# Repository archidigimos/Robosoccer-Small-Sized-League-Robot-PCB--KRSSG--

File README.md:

# Robosoccer-Small-Sized-League-Robot-PCB--KRSSG--
PCB for autonomous soccer playing robots. The PCBs are assembled in deck form.

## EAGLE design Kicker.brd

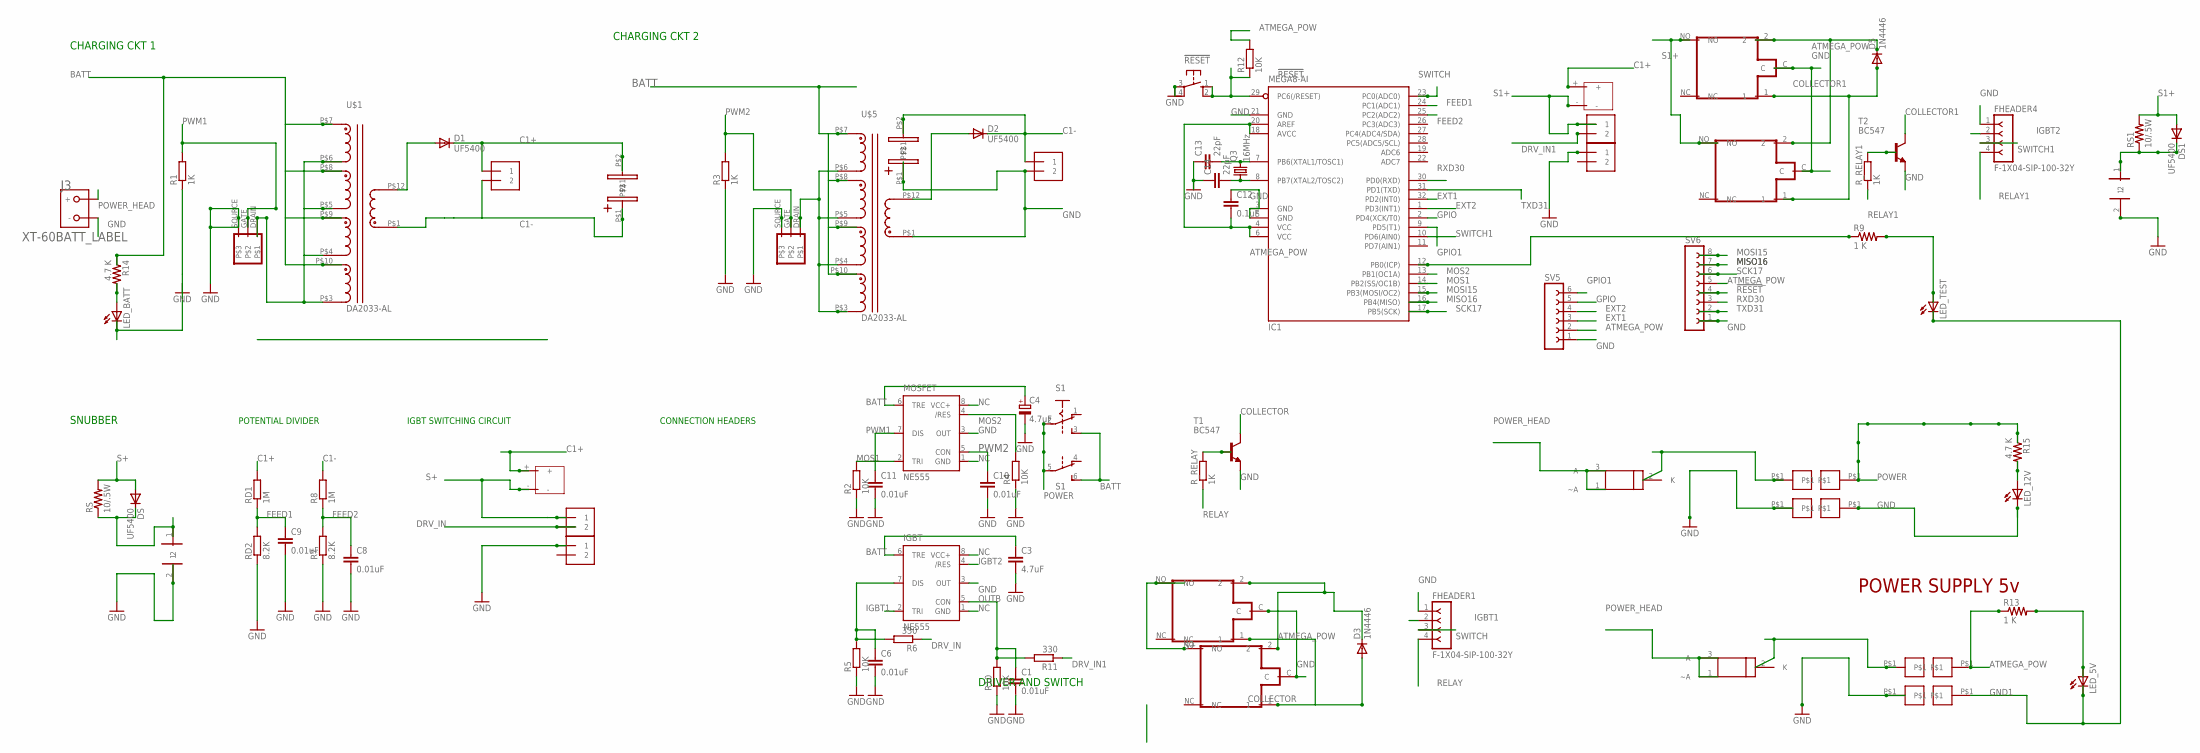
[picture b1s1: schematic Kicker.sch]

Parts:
5V: PINHEAD_1
!RESET: 10-XX; B3F-10XX
C1, C6, C8, C9, C10, C11: 0.01uF; C1206
C3: 4.7uF; C1206
C4: 4.7uF; E2,5-6
C12: 0.1uF; C1206
C13, C14: 22pF; C1206
D1, D2: UF5400; DO201-15
D3, D5: 1N4446; DO35-10
DS, DS1: UF5400; DO201-15
FHEADER1, FHEADER4: F-1X04-SIP-100-32Y; SIP-100-04-32Y
GND, GND12: PINHEAD_1
GND_5V, GND_12V1: PINHEAD_1
IC1: MEGA8-AI; TQFP32-08
IGBT: NE555; DIL-08
J1, J2, J4, J5, J6, J7: 1X2-3.5MM
J3: XT-60BATT_LABEL; XT-60
LED_5V, LED_12V: LEDSML1206; SML1206
LED_BATT: LEDSML1206; SML1206
LED_TEST: LEDSML1206; SML1206
MOSFET: NE555; DIL-08
POWER_1: PINHEAD_1
POWER_HEAD1: PINHEAD_1
Q3: 16MHz; HC49U70
R1, R3: 1K; R1206
R2, R4, R5, R10, R12: 10K; R1206
R6, R11: 330; R1206
R7: 8.2K; R1206
R8: 1M; R1206
R9, R13: 1 K; 0805-THM
R14, R15: 4.7 K; 0805-THM
RD1: 1M; R1206
RD2: 8.2K; R1206
RS, RS1: 10/.5W; 0411/15
R_RELAY, R_RELAY1: 1K; R1206
S1: A68-A31
SV5: FE06-1; FE06
SV6: FE08-1; FE08
T1, T2: BC547; TO92
U1, U4: LP38690DT-3.3; TO228P1042X238-3N
U$1, U$5: DA2033-AL
U$2, U$4: CAPS; CAP
U$3, U$9: MOS
U$6, U$16: SCREW
U$7, U$8: POLYCAP
U$10, U$11, U$12, U$13: REL
V_BAT: PINHEAD_1

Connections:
!RESET: !RESET.1 (S), !RESET.2 (S1), IC1.29 (PC6(/RESET)), R12.1, SV6.4
ATMEGA_POW: 5V.P$1, C12.2, D3.C, D5.C, IC1.4 (VCC), IC1.6 (VCC), IC1.18 (AVCC), IC1.20 (AREF), R12.2, R13.1, SV5.2, SV6.5, U$10.2, U$11.2, U$12.2, U$13.2
BATT: C3.1, C4.+, IGBT.6 (TRE), MOSFET.6 (TRE), R14.1, S1.3 (S), S1.6 (S), U$1.P$7 (7), U$1.P$8 (8), U$1.P$9 (9), U$1.P$10 (10), U$5.P$7 (7), U$5.P$8 (8), U$5.P$9 (9), U$5.P$10 (10)
C1+: D1.C, J2.1, RD1.2, U$2.P$2, U$6.+, U$16.+
C1-: D2.C, J1.1, J2.2, R8.2, U$1.P$1 (1), U$2.P$1, U$4.P$2
COLLECTOR: D3.A, T1.3 (C), U$10.1, U$12.1
COLLECTOR1: D5.A, T2.3 (C), U$11.1, U$13.1
DRV_IN: J6.2, R6.1
DRV_IN1: J4.2, R11.1
EXT1: IC1.32 (PD2(INT0)), SV5.3
EXT2: IC1.1 (PD3(INT1)), SV5.4
FEED1: C9.1, IC1.24 (PC1(ADC1)), RD1.1, RD2.2
FEED2: C8.1, IC1.25 (PC2(ADC2)), R7.2, R8.1
GND: !RESET.3, !RESET.4 (P1), C1.2, C3.2, C4.-, C6.2, C8.2, C9.2, C10.2, C11.2, C12.1, C13.1, C14.1, FHEADER1.1, FHEADER4.1, GND12.P$1, GND_5V.P$1, GND_12V1.P$1, IC1.3 (GND), IC1.5 (GND), IC1.21 (GND), IGBT.3 (OUT), J1.2, J3.GND (-), J5.1, J7.1, LED_12V.C, LED_BATT.C, MOSFET.3 (OUT), R1.1, R2.1, R3.1, R4.1, R5.1, R7.1, R10.1, RD2.1, SV5.1, SV6.1, T1.1 (E), T2.1 (E), U$3.SOURCE, U$4.P$1, U$5.P$1 (1), U$7.2, U$8.2, U$9.SOURCE, U$10.C, U$11.C, U$12.C, U$13.C
GND1: GND.P$1, LED_5V.C, LED_TEST.C
GPIO: IC1.2 (PD4(XCK/T0)), SV5.5
GPIO1: IC1.9 (PD5(T1)), SV5.6
IGBT1: FHEADER1.2, IGBT.2 (TRI)
IGBT2: FHEADER4.2, IGBT.4 (/RES)
MISO16: IC1.16 (PB4(MISO)), SV6.7
MOS1: IC1.14 (PB2(SS/OC1B)), MOSFET.2 (TRI), R2.2
MOS2: IC1.13 (PB1(OC1A)), MOSFET.4 (/RES), R4.2
MOSI15: IC1.15 (PB3(MOSI/OC2)), SV6.8
unnamed: DS.C, RS.1, U$7.1
unnamed: R_RELAY.2, T1.2 (B)
unnamed: C6.1, IGBT.7 (DIS), R5.2, R6.2
unnamed: D2.A, U$5.P$12 (12)
unnamed: LED_5V.A, R13.2
unnamed: POWER_HEAD1.P$1, U1.2 (K)
unnamed: D1.A, U$1.P$12 (12)
unnamed: DS1.C, RS1.1, U$8.1
unnamed: R_RELAY1.2, T2.2 (B)
unnamed: LED_BATT.A, R14.2
unnamed: C13.2, IC1.7 (PB6(XTAL1/TOSC1)), Q3.2
unnamed: LED_12V.A, R15.2
unnamed: U4.2 (K), V_BAT.P$1
unnamed: C14.2, IC1.8 (PB7(XTAL2/TOSC2)), Q3.1
unnamed: LED_TEST.A, R9.2
unnamed: U$5.P$3 (3), U$5.P$4 (4), U$5.P$5 (5), U$5.P$6 (6), U$9.DRAIN
unnamed: U$1.P$3 (3), U$1.P$4 (4), U$1.P$5 (5), U$1.P$6 (6), U$3.DRAIN
unnamed: IC1.12 (PB0(ICP)), R9.1
NC: IGBT.1 (GND), IGBT.8 (VCC+), MOSFET.1 (GND), MOSFET.8 (VCC+)
OUTB: C1.1, IGBT.5 (CON), R10.2, R11.2
POWER: POWER_1.P$1, R15.1, S1.2, S1.5
POWER_HEAD: J3.BATT (+), U1.1 (~A), U1.3 (A), U4.1 (~A), U4.3 (A)
PWM1: C11.1, MOSFET.7 (DIS), R1.2, U$3.GATE
PWM2: C10.1, MOSFET.5 (CON), R3.2, U$9.GATE
RELAY: FHEADER1.4, R_RELAY.1
RELAY1: FHEADER4.4, R_RELAY1.1
RXD30: IC1.30 (PD0(RXD)), SV6.3
S1+: DS1.A, J4.1, RS1.2, U$6.-, U$11.NO, U$13.NO
S+: DS.A, J6.1, RS.2, U$10.NO, U$12.NO, U$16.-
SCK17: IC1.17 (PB5(SCK)), SV6.6
SWITCH: FHEADER1.3, IC1.23 (PC0(ADC0))
SWITCH1: FHEADER4.3, IC1.10 (PD6(AIN0))
TXD31: IC1.31 (PD1(TXD)), SV6.2

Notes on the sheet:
SNUBBER
CHARGING CKT 1
CHARGING CKT 2
POTENTIAL DIVIDER
IGBT SWITCHING CIRCUIT
CONNECTION HEADERS
DRIVER AND SWITCH
POWER SUPPLY 5v

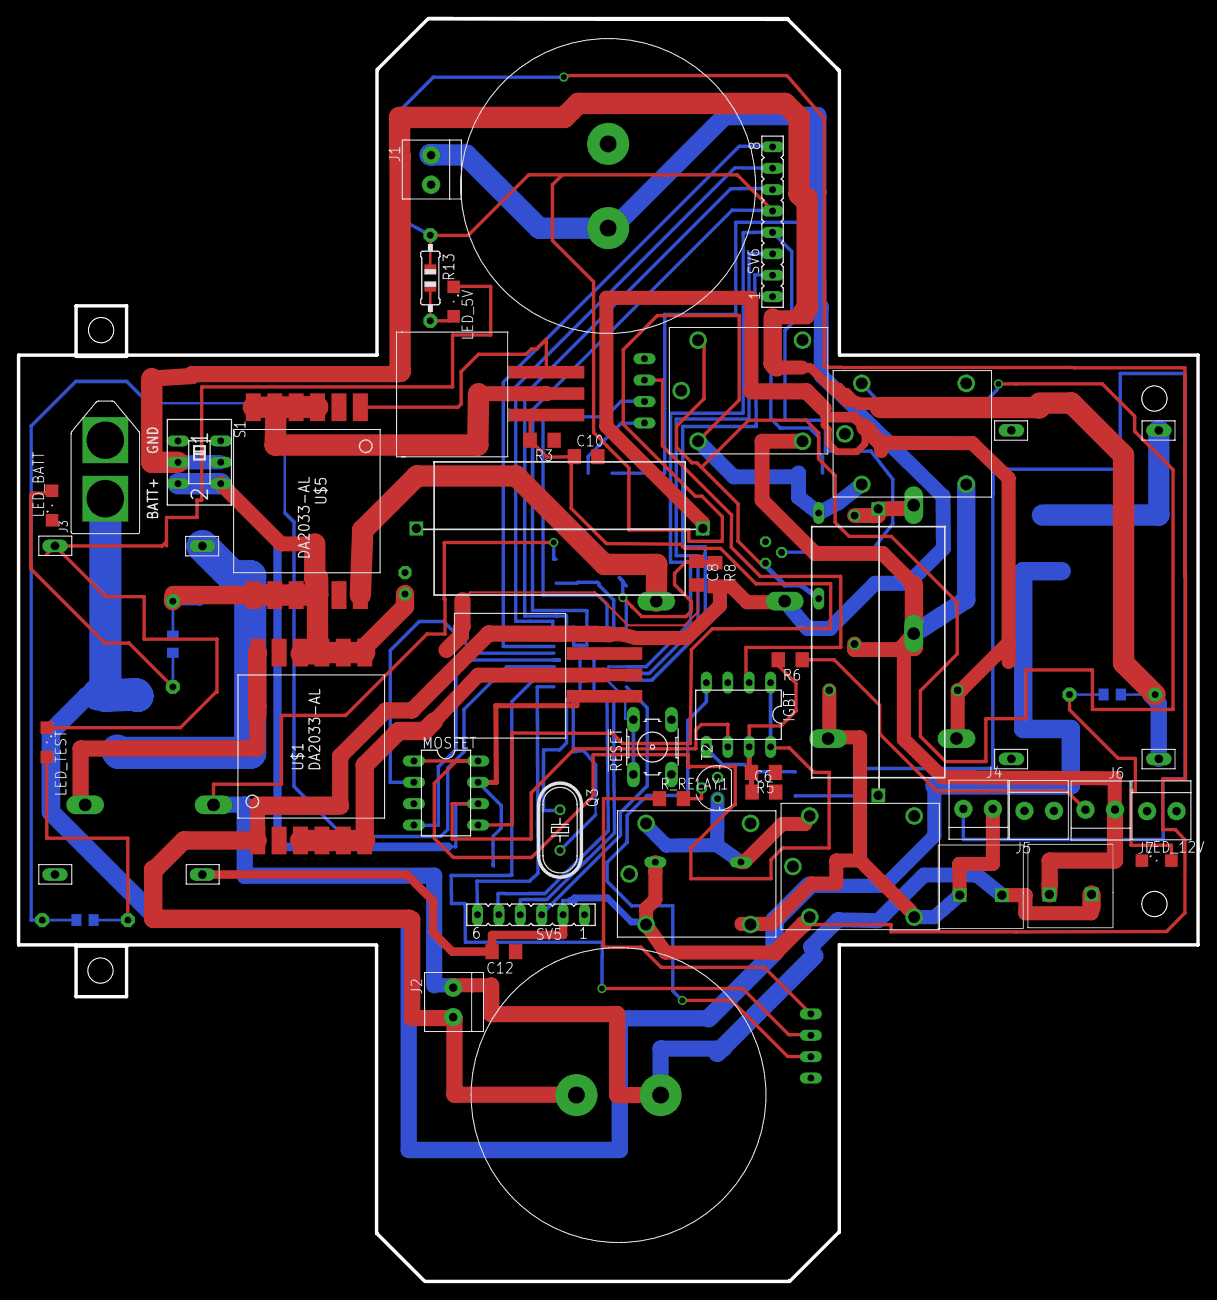
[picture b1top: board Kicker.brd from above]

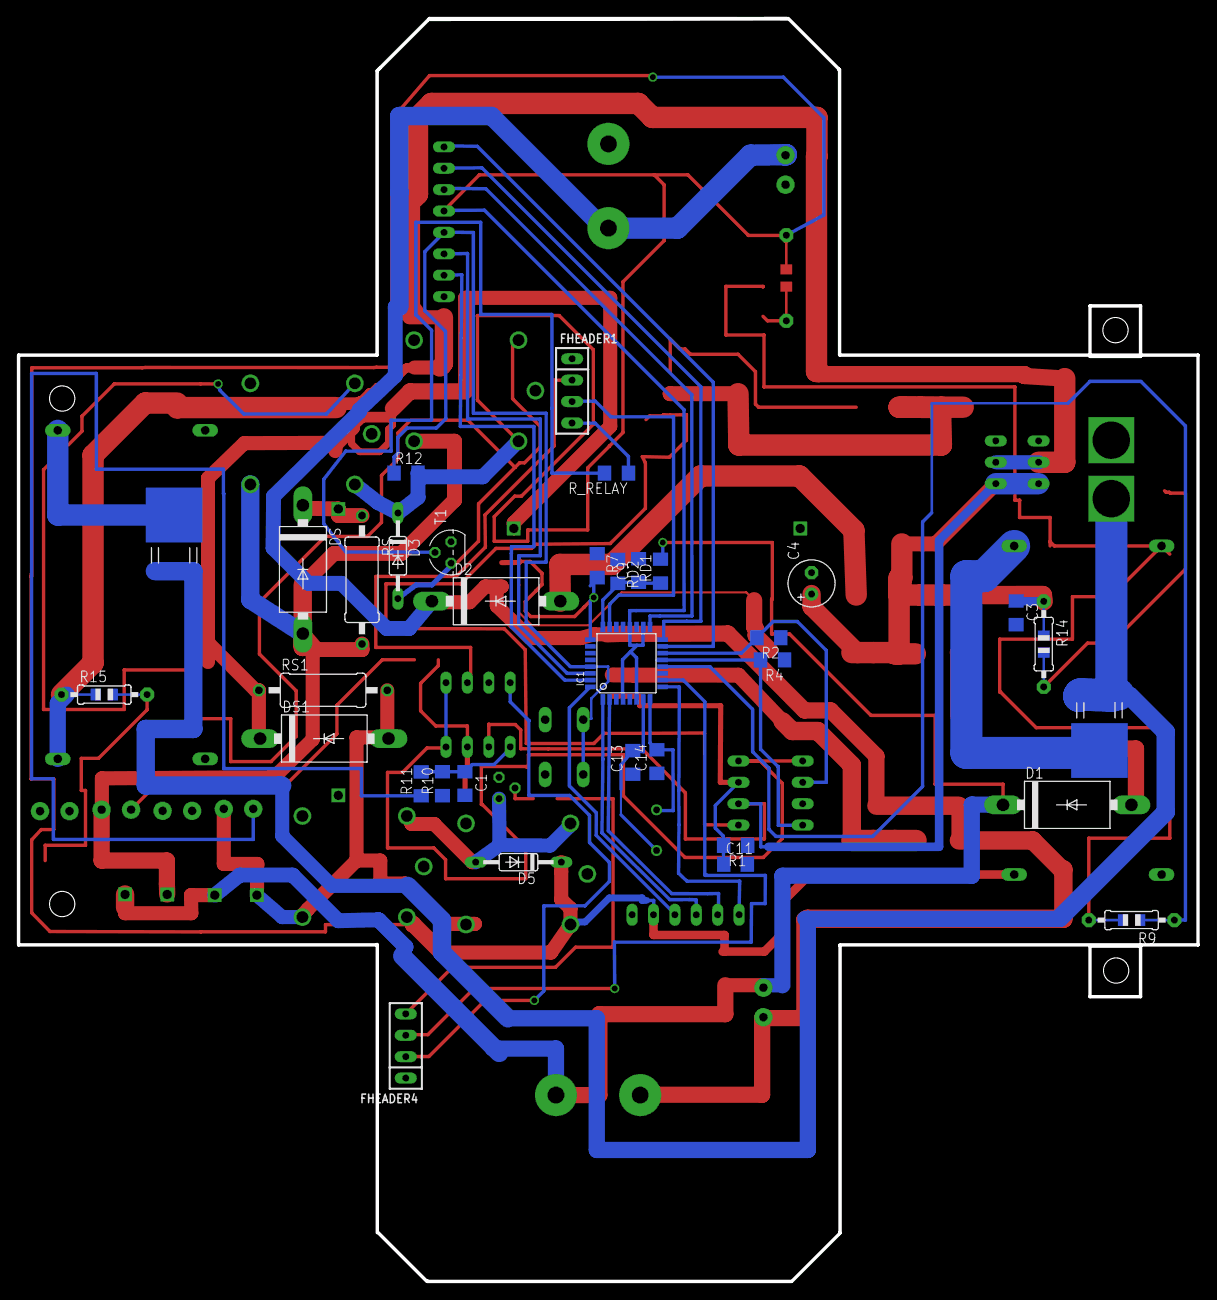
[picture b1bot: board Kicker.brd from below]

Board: 2 copper layers, 140.0 x 149.9 mm, 85 parts (34 on the bottom side), 56 nets.

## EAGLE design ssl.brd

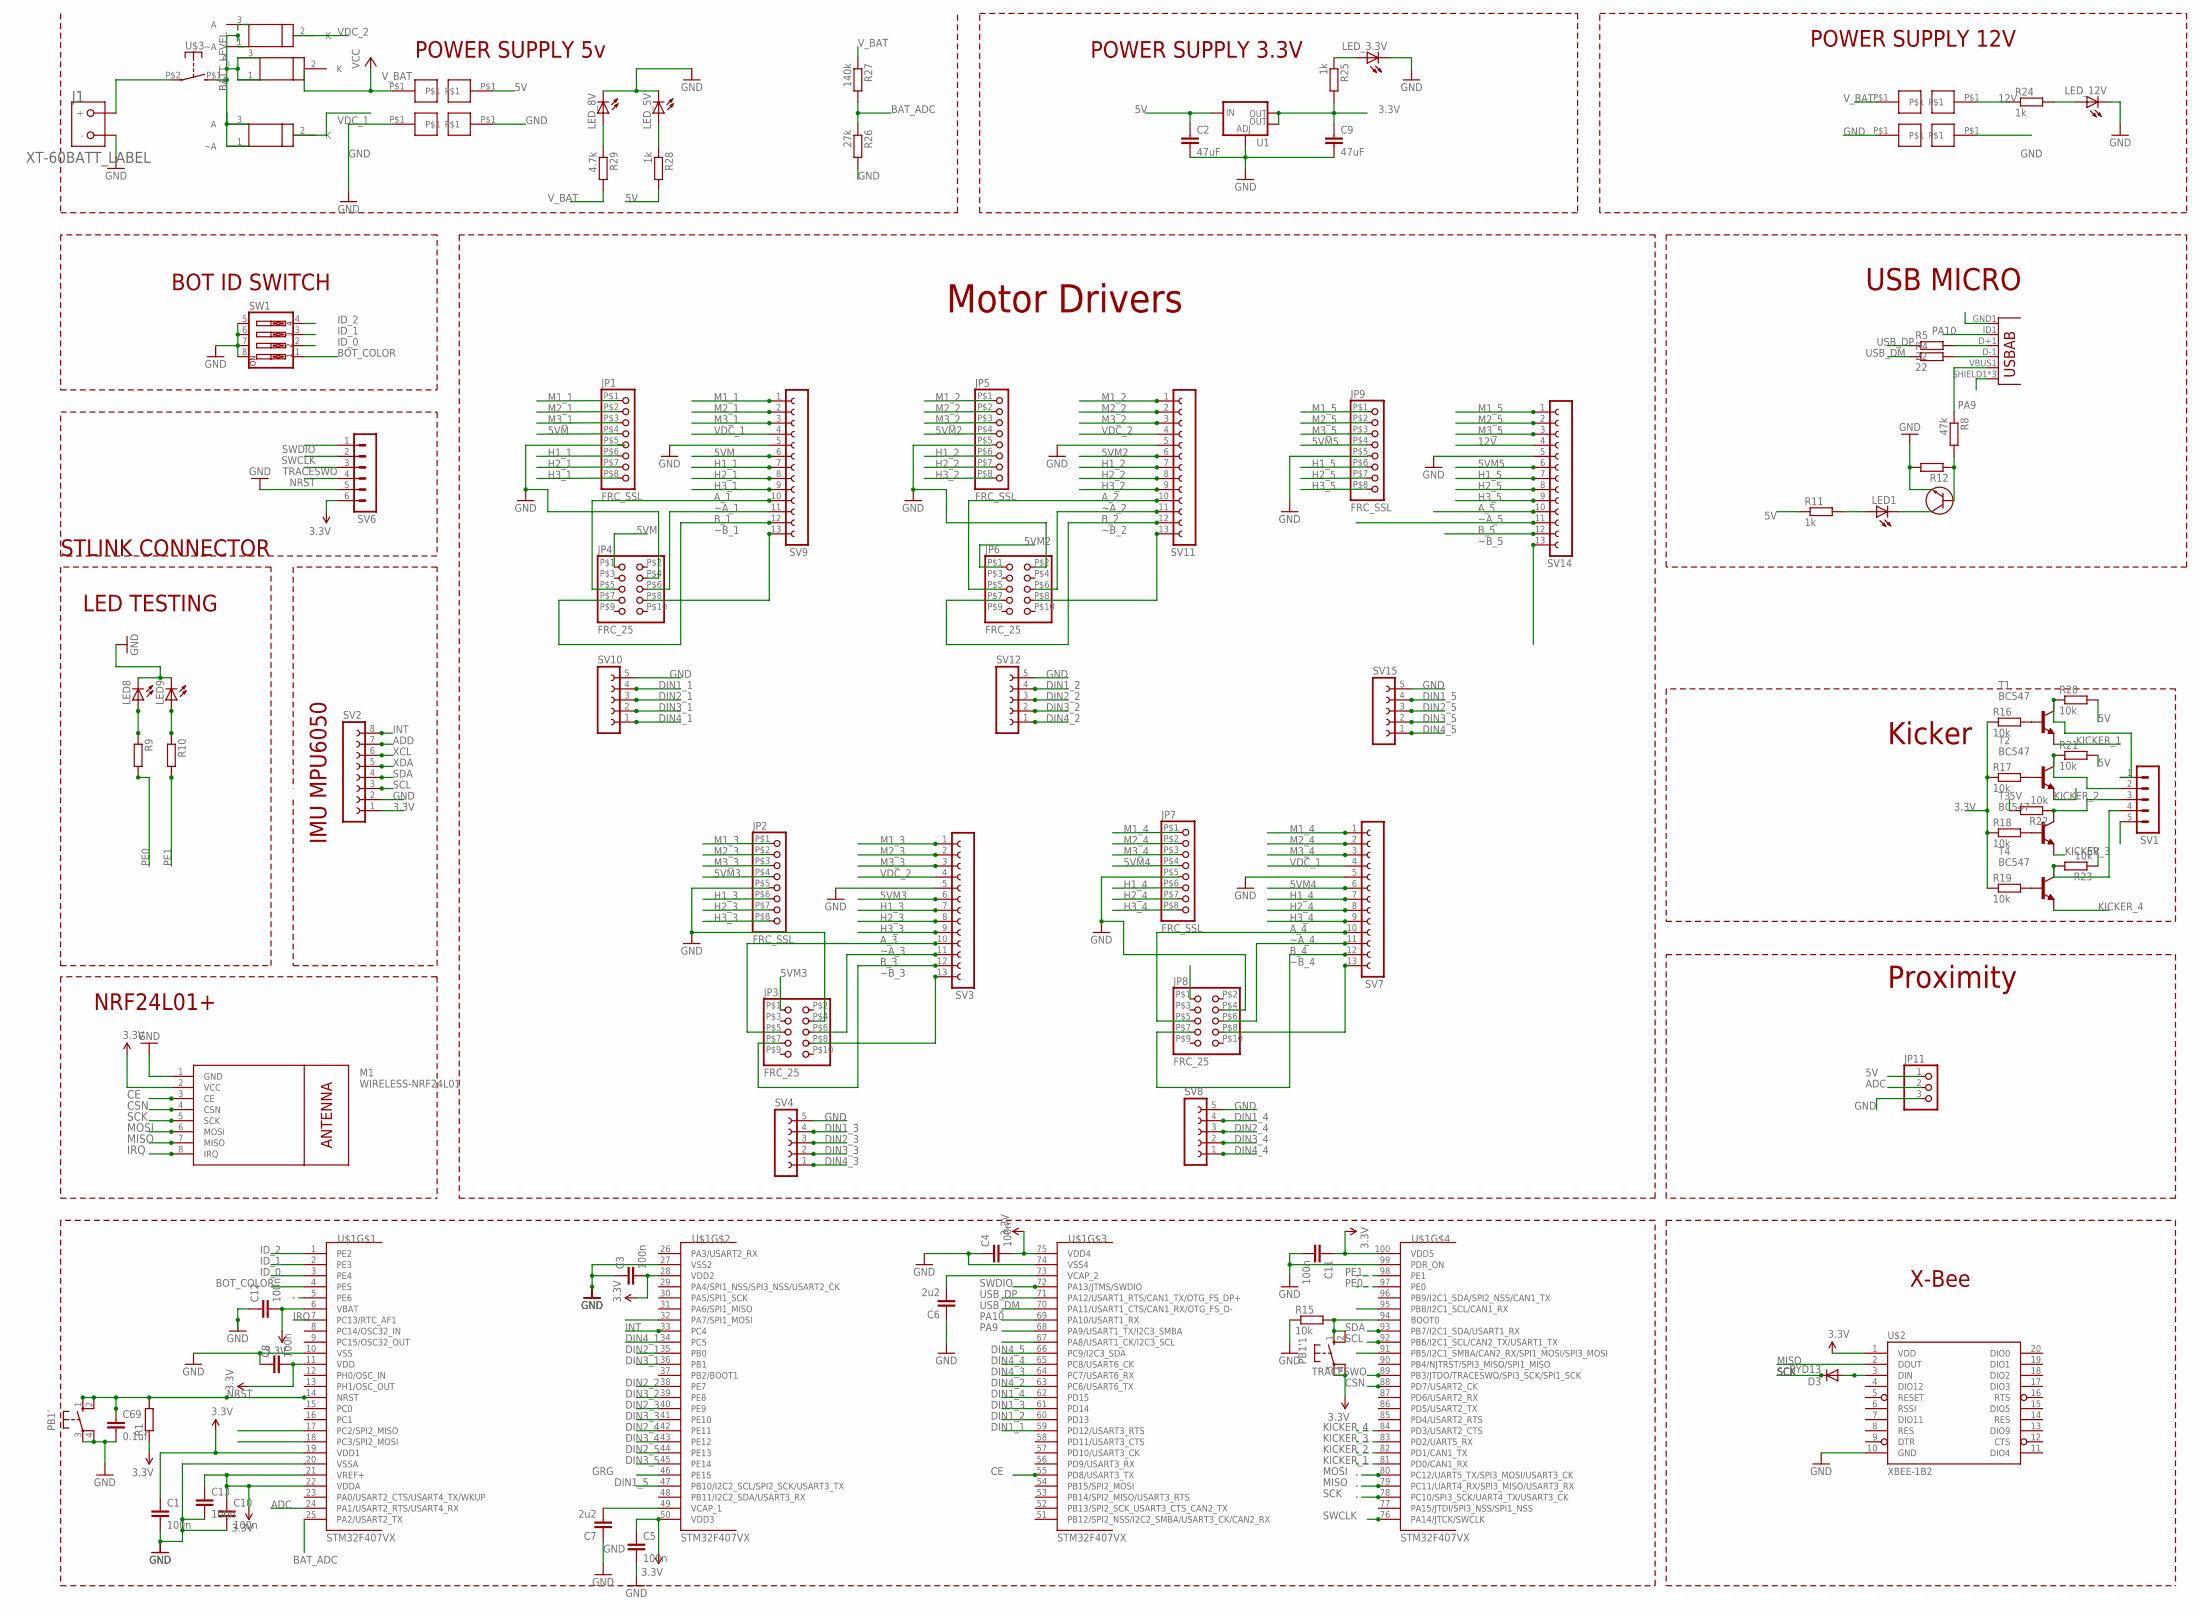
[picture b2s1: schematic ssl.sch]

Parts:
5V, 12V: PINHEAD_1
C1, C3, C4, C5, C8, C10, C11, C12, C13: 100n; C1206
C2, C9: 47uF; C1206
C6, C7: 2u2; C1206
C69: 0.1uf; C1206
D3: BYD13; SOD81
GND, GND2: PINHEAD_1
GND_5V, GND_12V: PINHEAD_1
J1: XT-60BATT_LABEL; XT-60
JP1, JP2, JP5, JP7, JP9: FRC_SSL; FRC
JP3, JP4, JP6, JP8: FRC_25; FRC2*5
JP11: PINHD-1X3; 1X03
LED1, LED8, LED9: LEDCHIPLED_1206; CHIPLED_1206
LED_3.3V, LED_5V, LED_8V, LED_12V: LEDCHIPLED_1206; CHIPLED_1206
M1: WIRELESS-NRF24L01
PB1', PB1'1: 10-XX; B3F-10XX
Q1: TRANSISTOR-NPN-TO-92-EBC; TO-92
R1: R-EU_M0805; M0805
R4, R5: 22; R1206
R8: 47k; R1206
R9, R10, R12: R-EU_R1206; R1206
R11, R24, R25, R28: 1k; R1206
R15, R16, R17, R18, R19, R20, R21, R22, R23: 10k; R1206
R26: 27k; R1206
R27: 140k; R1206
R29: 4.7k; R1206
SV1: MA05-1
SV2: FE08-1; FE08
SV3, SV7, SV9, SV11, SV14: FE13-1; FE13
SV4, SV8, SV10, SV12, SV15: FE05-1
SV6: MA06-1
SW1: SW_DIP-4; EDG-04
T1, T2, T3, T4: BC547; TO92
U1: V_REG_LM1117SOT223; SOT223
U2, U3, U4: LP38690DT-3.3; TO228P1042X238-3N
U5: USB-ABCONN-11794; USB-AB-MICRO-SMD_V03
U$1: STM32F407VX; LQFP100
U$2: XBEE-1B2; XBEE-SILK
U$3: SWITCH_DA10; DA10
V_BAT: PINHEAD_1
V_BAT_12V: PINHEAD_1

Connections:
3.3V: C1.1, C3.2, C4.2, C5.1, C8.2, C9.1, C10.1, C11.1, C12.2, C13.1, M1.2 (VCC), PB1'1.3, PB1'1.4 (P1), Q1.1 (E), R1.1, R12.2, R16.1, R17.1, R18.1, R19.1, R25.2, SV2.1, SV6.6, U1.2 (OUT), U1.4 (OUT), U$1.6 (VBAT), U$1.11 (VDD), U$1.19 (VDD1), U$1.21 (VREF+), U$1.22 (VDDA), U$1.28 (VDD2), U$1.50 (VDD3), U$1.75 (VDD4), U$1.100 (VDD5), U$2.1 (VDD)
5V: 5V.P$1, C2.1, JP11.1, R11.1, R20.2, R21.2, R22.2, R23.1, R28.2, U1.3 (IN)
5VM: JP1.P$4 (4), JP4.P$1 (1), SV9.6
5VM2: JP5.P$4 (4), JP6.P$1 (1), SV11.6
5VM3: JP2.P$4 (4), JP3.P$1 (1), SV3.6
5VM4: JP7.P$4 (4), JP8.P$1 (1), SV7.6
5VM5: JP9.P$4 (4), SV14.6
12V: 12V.P$1, R24.1, SV14.4
ADC: JP11.2, U$1.24 (PA1/USART2_RTS/USART4_RX)
ADD: SV2.7
A_1: JP4.P$5 (5), SV9.10
A_2: JP6.P$5 (5), SV11.10
A_3: JP3.P$5 (5), SV3.10
A_4: JP8.P$5 (5), SV7.10
A_5: SV14.10
BATTERY: J1.BATT (+), U$3.P$2
BATT_LEVEL: U2.1 (~A), U2.3 (A), U3.1 (~A), U3.3 (A), U4.1 (~A), U4.3 (A), U$3.P$1 (S)
BAT_ADC: R26.1, R27.2, U$1.25 (PA2/USART2_TX)
BOT_COLOR: SW1.1, U$1.4 (PE5)
B_1: JP4.P$7 (7), SV9.12
B_2: JP6.P$7 (7), SV11.12
B_3: JP3.P$7 (7), SV3.12
B_4: JP8.P$7 (7), SV7.12
B_5: SV14.12
CE: M1.3 (CE), U$1.55 (PD8/USART3_TX)
CSN: M1.4 (CSN), U$1.88 (PD7/USART2_CK)
DIN1_1: SV10.4, U$1.59 (PD12/USART3_RTS)
DIN1_2: SV12.4, U$1.60 (PD13)
DIN1_3: SV4.4, U$1.61 (PD14)
DIN1_4: SV8.4, U$1.62 (PD15)
DIN1_5: SV15.4, U$1.47 (PB10/I2C2_SCL/SPI2_SCK/USART3_TX)
DIN2_1: SV10.3, U$1.35 (PB0)
DIN2_2: SV12.3, U$1.38 (PE7)
DIN2_3: SV4.3, U$1.40 (PE9)
DIN2_4: SV8.3, U$1.42 (PE11)
DIN2_5: SV15.3, U$1.44 (PE13)
DIN3_1: SV10.2, U$1.36 (PB1)
DIN3_2: SV12.2, U$1.39 (PE8)
DIN3_3: SV4.2, U$1.41 (PE10)
DIN3_4: SV8.2, U$1.43 (PE12)
DIN3_5: SV15.2, U$1.45 (PE14)
DIN4_1: SV10.1, U$1.34 (PC5)
DIN4_2: SV12.1, U$1.63 (PC6/USART6_TX)
DIN4_3: SV4.1, U$1.64 (PC7/USART6_RX)
DIN4_4: SV8.1, U$1.65 (PC8/USART6_CK)
DIN4_5: SV15.1, U$1.66 (PC9/I2C3_SDA)
GND: C1.2, C2.2, C3.1, C4.1, C5.2, C6.1, C7.1, C8.1, C9.2, C10.2, C11.2, C12.1, C13.2, C69.2, GND.P$1, GND2.P$1, GND_5V.P$1, GND_12V.P$1, J1.GND (-), JP3.P$4 (4), JP4.P$4 (4), JP6.P$2 (2), JP8.P$4 (4), JP11.3, LED8.C, LED9.C, LED_3.3V.C, LED_5V.C, LED_8V.C, LED_12V.C, M1.1 (GND), PB1'.3, PB1'.4 (P1), R15.1, R26.2, SV1.5, SV2.2, SV3.5, SV4.5, SV6.5, SV7.5, SV8.5, SV9.5, SV10.5, SV11.5, SV12.5, SV14.5, SV15.5, SW1.5, SW1.6, SW1.7, SW1.8, U1.1 (ADJ), U5.GND1 (GND), U5.SHIELD1 (SHIELD), U5.SHIELD2 (SHIELD), U5.SHIELD3 (SHIELD), U$1.10 (VSS), U$1.20 (VSSA), U$1.27 (VSS2), U$1.74 (VSS4), U$1.99 (PDR_ON), U$2.10 (GND)
GRG: U$1.46 (PE15)
H1_1: JP1.P$6 (6), SV9.7
H1_2: JP5.P$6 (6), SV11.7
H1_3: JP2.P$6 (6), SV3.7
H1_4: JP7.P$6 (6), SV7.7
H1_5: JP9.P$6 (6), SV14.7
H2_1: JP1.P$7 (7), SV9.8
H2_2: JP5.P$7 (7), SV11.8
H2_3: JP2.P$7 (7), SV3.8
H2_4: JP7.P$7 (7), SV7.8
H2_5: JP9.P$7 (7), SV14.8
H3_1: JP1.P$8 (8), SV9.9
H3_2: JP5.P$8 (8), SV11.9
H3_3: JP2.P$8 (8), SV3.9
H3_4: JP7.P$8 (8), SV7.9
H3_5: JP9.P$8 (8), SV14.9
ID_0: SW1.2, U$1.3 (PE4)
ID_1: SW1.3, U$1.2 (PE3)
ID_2: SW1.4, U$1.1 (PE2)
INT: SV2.8, U$1.33 (PC4)
IRQ: M1.8 (IRQ), U$1.7 (PC13/RTC_AF1)
KICKER_1: T1.1 (E), U$1.81 (PD0/CAN1_RX)
KICKER_2: T2.1 (E), U$1.82 (PD1/CAN1_TX)
KICKER_3: T3.1 (E), U$1.83 (PD2/UART5_RX)
KICKER_4: T4.1 (E), U$1.84 (PD3/USART2_CTS)
M1_1: JP1.P$1 (1), SV9.1
M1_2: JP5.P$1 (1), SV11.1
M1_3: JP2.P$1 (1), SV3.1
M1_4: JP7.P$1 (1), SV7.1
M1_5: JP9.P$1 (1), SV14.1
M2_1: JP1.P$2 (2), SV9.2
M2_2: JP5.P$2 (2), SV11.2
M2_3: JP2.P$2 (2), SV3.2
M2_4: JP7.P$2 (2), SV7.2
M2_5: JP9.P$2 (2), SV14.2
M3_1: JP1.P$3 (3), SV9.3
M3_2: JP5.P$3 (3), SV11.3
M3_3: JP2.P$3 (3), SV3.3
M3_4: JP7.P$3 (3), SV7.3
M3_5: JP9.P$3 (3), SV14.3
MISO: M1.7 (MISO), U$1.79 (PC11/UART4_RX/SPI3_MISO/USART3_RX), U$2.2 (DOUT)
MOSI: M1.6 (MOSI), U$1.80 (PC12/UART5_TX/SPI3_MOSI/USART3_CK)
unnamed: R5.2, U5.D+1 (D+)
unnamed: LED9.A, R10.1
unnamed: C7.2, U$1.49 (VCAP_1)
unnamed: C6.2, U$1.73 (VCAP_2)
unnamed: R4.2, U5.D-1 (D-)
unnamed: PB1'1.1 (S), PB1'1.2 (S1), R15.2, U$1.94 (BOOT0)
unnamed: LED8.A, R9.1
unnamed: Q1.2 (B), R8.2, R12.1
unnamed: LED1.C, Q1.3 (C)
unnamed: D3.A, U$2.3 (DIN)
unnamed: LED1.A, R11.2
unnamed: LED_12V.A, R24.2
unnamed: LED_8V.A, R29.1
unnamed: LED_5V.A, R28.1
unnamed: LED_3.3V.A, R25.1
unnamed: R18.2, T3.2 (B)
unnamed: R16.2, T1.2 (B)
unnamed: R17.2, T2.2 (B)
unnamed: R19.2, T4.2 (B)
unnamed: R20.1, SV1.1, T1.3 (C)
unnamed: R21.1, SV1.2, T2.3 (C)
unnamed: R22.1, SV1.3, T3.3 (C)
unnamed: R23.2, SV1.4, T4.3 (C)
NRST: C69.1, PB1'.1 (S), PB1'.2 (S1), R1.2, SV6.4, U$1.14 (NRST)
PA9: R8.1, U5.VBUS1 (VBUS), U$1.68 (PA9/USART1_TX/I2C3_SMBA)
PA10: U5.ID1 (USBID), U$1.69 (PA10/USART1_RX)
PE0: R9.2, U$1.97 (PE0)
PE1: R10.2, U$1.98 (PE1)
SCK: D3.C, M1.5 (SCK), U$1.78 (PC10/SPI3_SCK/UART4_TX/USART3_CK)
SCL: SV2.3, U$1.92 (PB6/I2C1_SCL/CAN2_TX/USART1_TX)
SDA: SV2.4, U$1.93 (PB7/I2C1_SDA/USART1_RX)
SWCLK: SV6.2, U$1.76 (PA14/JTCK/SWCLK)
SWDIO: SV6.1, U$1.72 (PA13/JTMS/SWDIO)
TRACESWO: SV6.3, U$1.89 (PB3/JTDO/TRACESWO/SPI3_SCK/SPI1_SCK)
USB_DM: R4.1, U$1.70 (PA11/USART1_CTS/CAN1_RX/OTG_FS_D-)
USB_DP: R5.1, U$1.71 (PA12/USART1_RTS/CAN1_TX/OTG_FS_DP+)
VDC_1: SV7.4, SV9.4, U4.2 (K)
VDC_2: SV3.4, SV11.4, U3.2 (K)
V_BAT: R27.1, R29.2, U2.2 (K), V_BAT.P$1, V_BAT_12V.P$1
XCL: SV2.6
XDA: SV2.5
~A_1: JP4.P$6 (6), SV9.11
~A_2: JP6.P$6 (6), SV11.11
~A_3: JP3.P$6 (6), SV3.11
~A_4: JP8.P$6 (6), SV7.11
~A_5: SV14.11
~B_1: JP4.P$8 (8), SV9.13
~B_2: JP6.P$8 (8), SV11.13
~B_3: JP3.P$8 (8), SV3.13
~B_4: JP8.P$8 (8), SV7.13
~B_5: SV14.13

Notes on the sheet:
NRF24L01+
BOT ID SWITCH
STLINK CONNECTOR
IMU MPU6050
POWER SUPPLY 5v
LED TESTING
Motor Drivers
POWER SUPPLY 12V
POWER SUPPLY 3.3V
X-Bee
Proximity
USB MICRO
Kicker

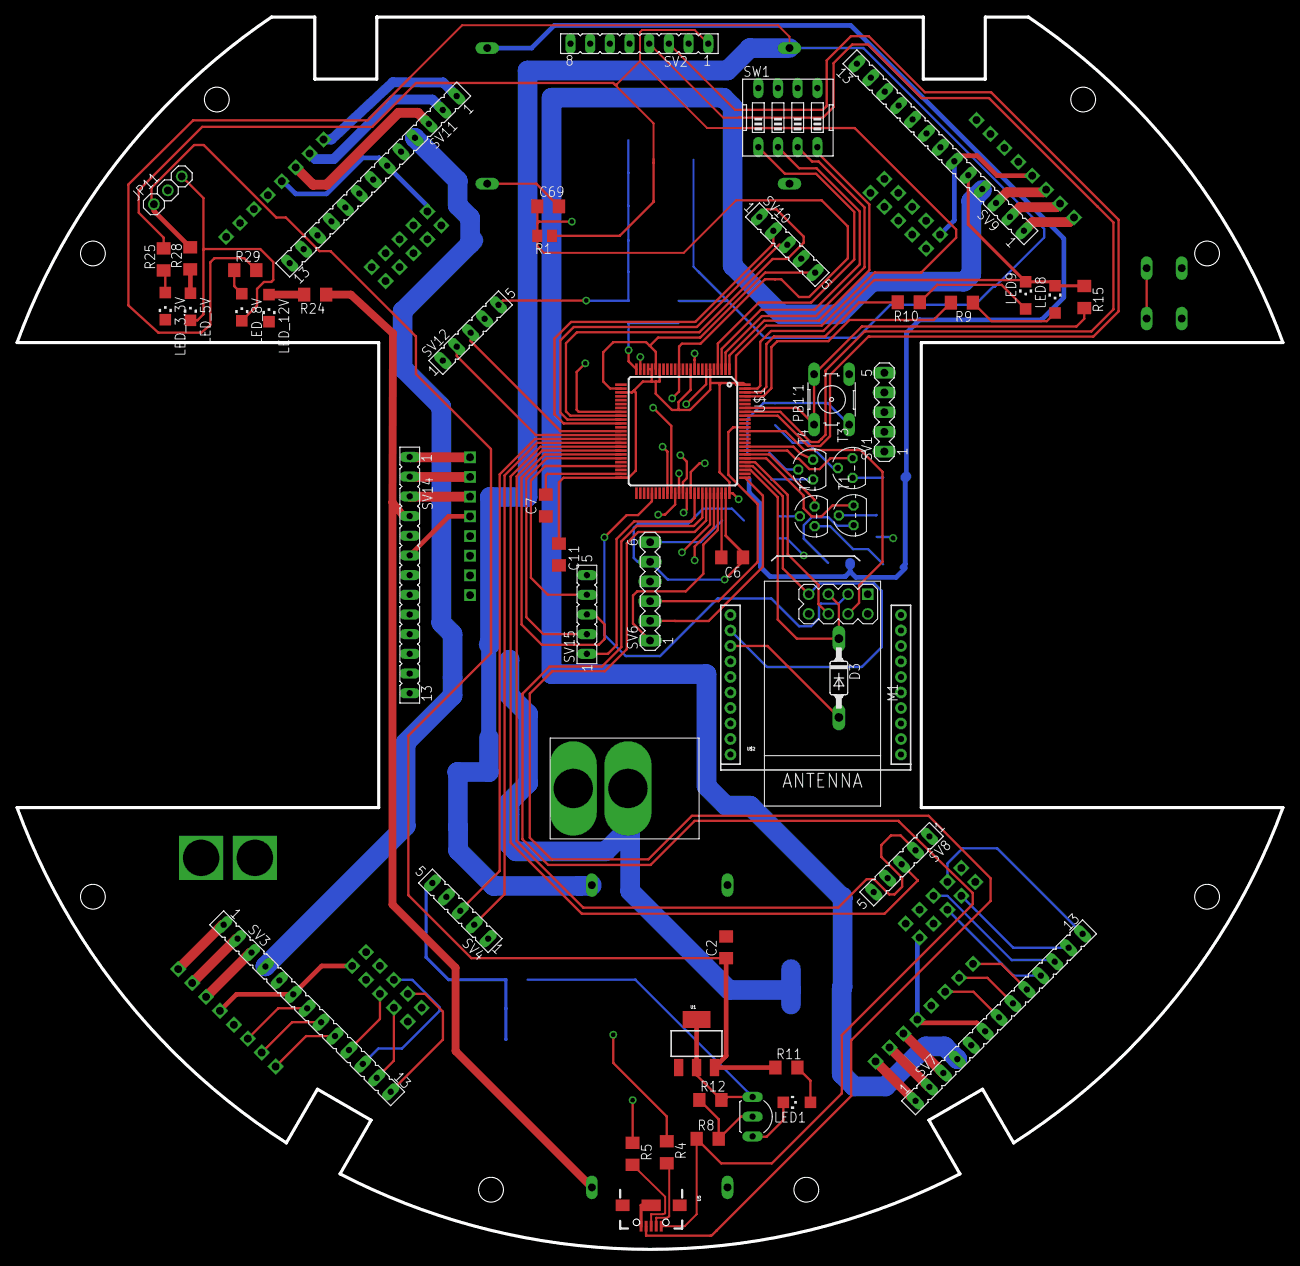
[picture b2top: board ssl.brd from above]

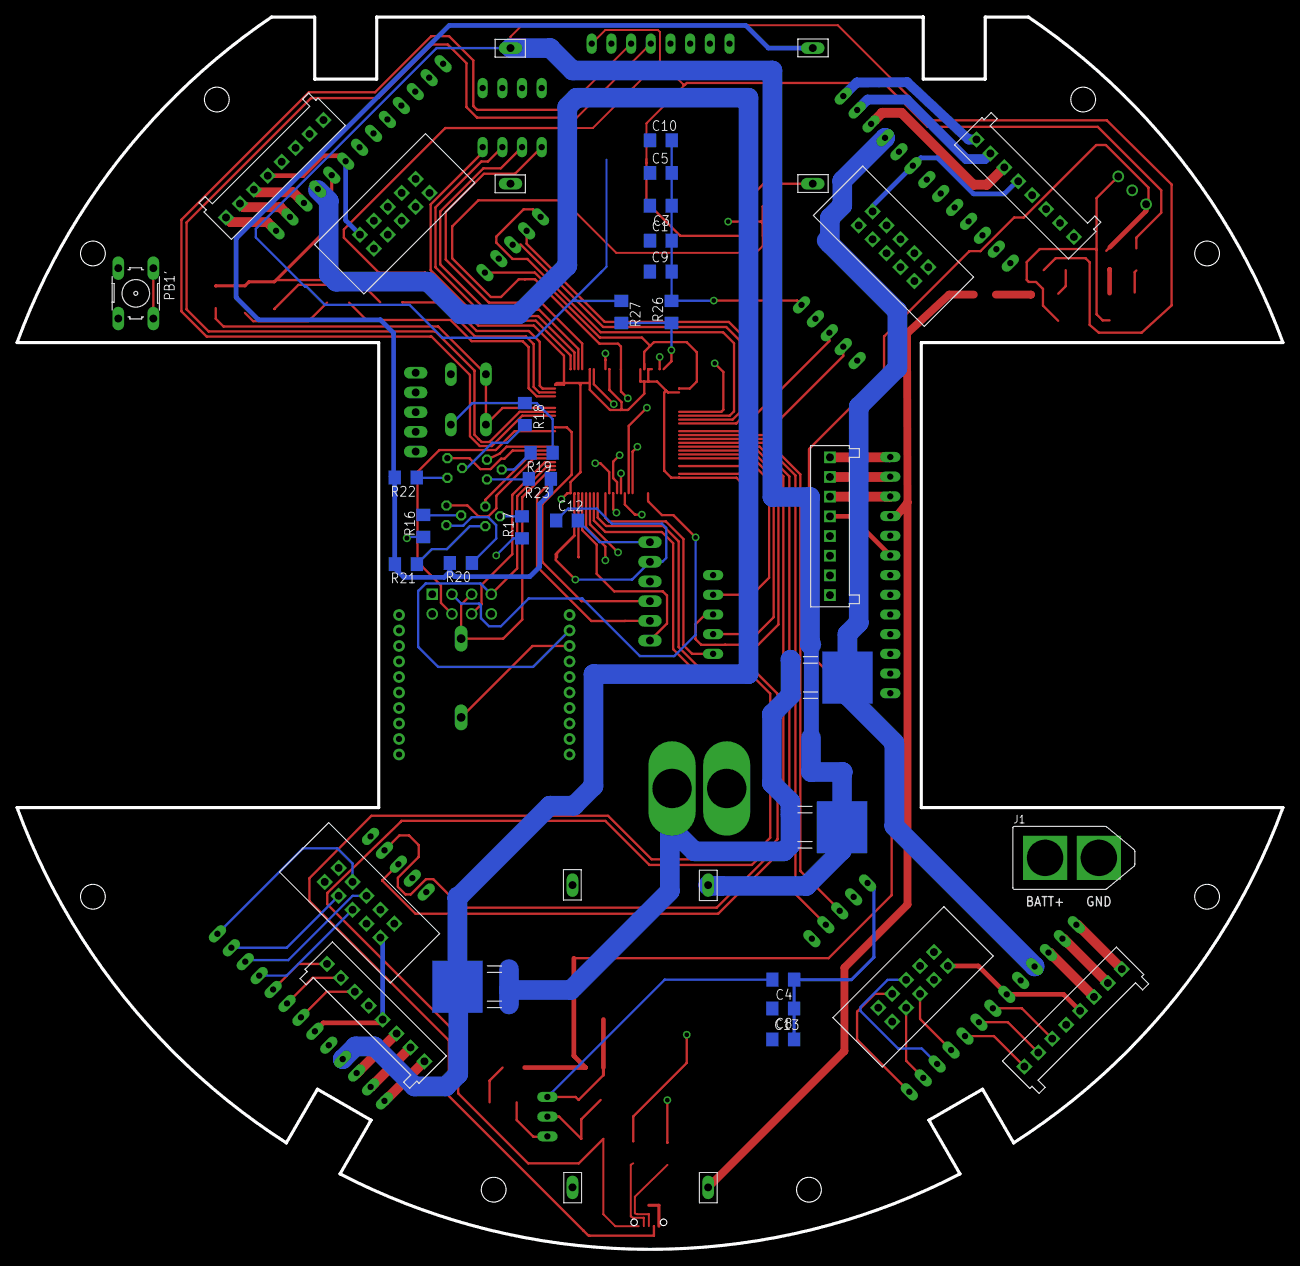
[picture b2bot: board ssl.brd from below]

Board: 4 copper layers, 163.3 x 159.0 mm, 94 parts (41 on the bottom side), 132 nets.

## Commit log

2017-08-08 :circus_tent: Added .gitattributes & .gitignore files
2017-08-08 Screenshot

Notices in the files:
parts and their libraries:
con-headers-jp: Copyright (C) 2008, Bob Starr
SparkFun: Licensing: CC v3.0 Share-Alike You are welcome to use this library for commercial purposes.
SparkFun-PowerIC: Licensing: Creative Commons ShareAlike 4.0 International - https://creativecommons.org/licenses/by-sa/4.0
